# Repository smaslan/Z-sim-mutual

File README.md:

# Capacitive Reactance Simulator Based on Mutual Inductor

This project is simple simulator of capacitive rectance based on a mutual inductor.
It is just a first proof of concept prototype not inteded for direct production/replication.
See DOC for known issues and more details.

## License
The HW design is distributed under [Cern OHL license V1.2](./cern_ohl_v_1_2.pdf). 

## Acknowledgment
Presented standard design was co-developed in scope of the [EMPIR](http://msu.euramet.org/calls.html) 
project [LiBforSecUse (17IND10)](https://www.ptb.de/empir2018/libforsecuse/home/).
The project received funding from the EMPIR programme co-financed by the Participating States 
and from the European Union's Horizon 2020 research and innovation programme.

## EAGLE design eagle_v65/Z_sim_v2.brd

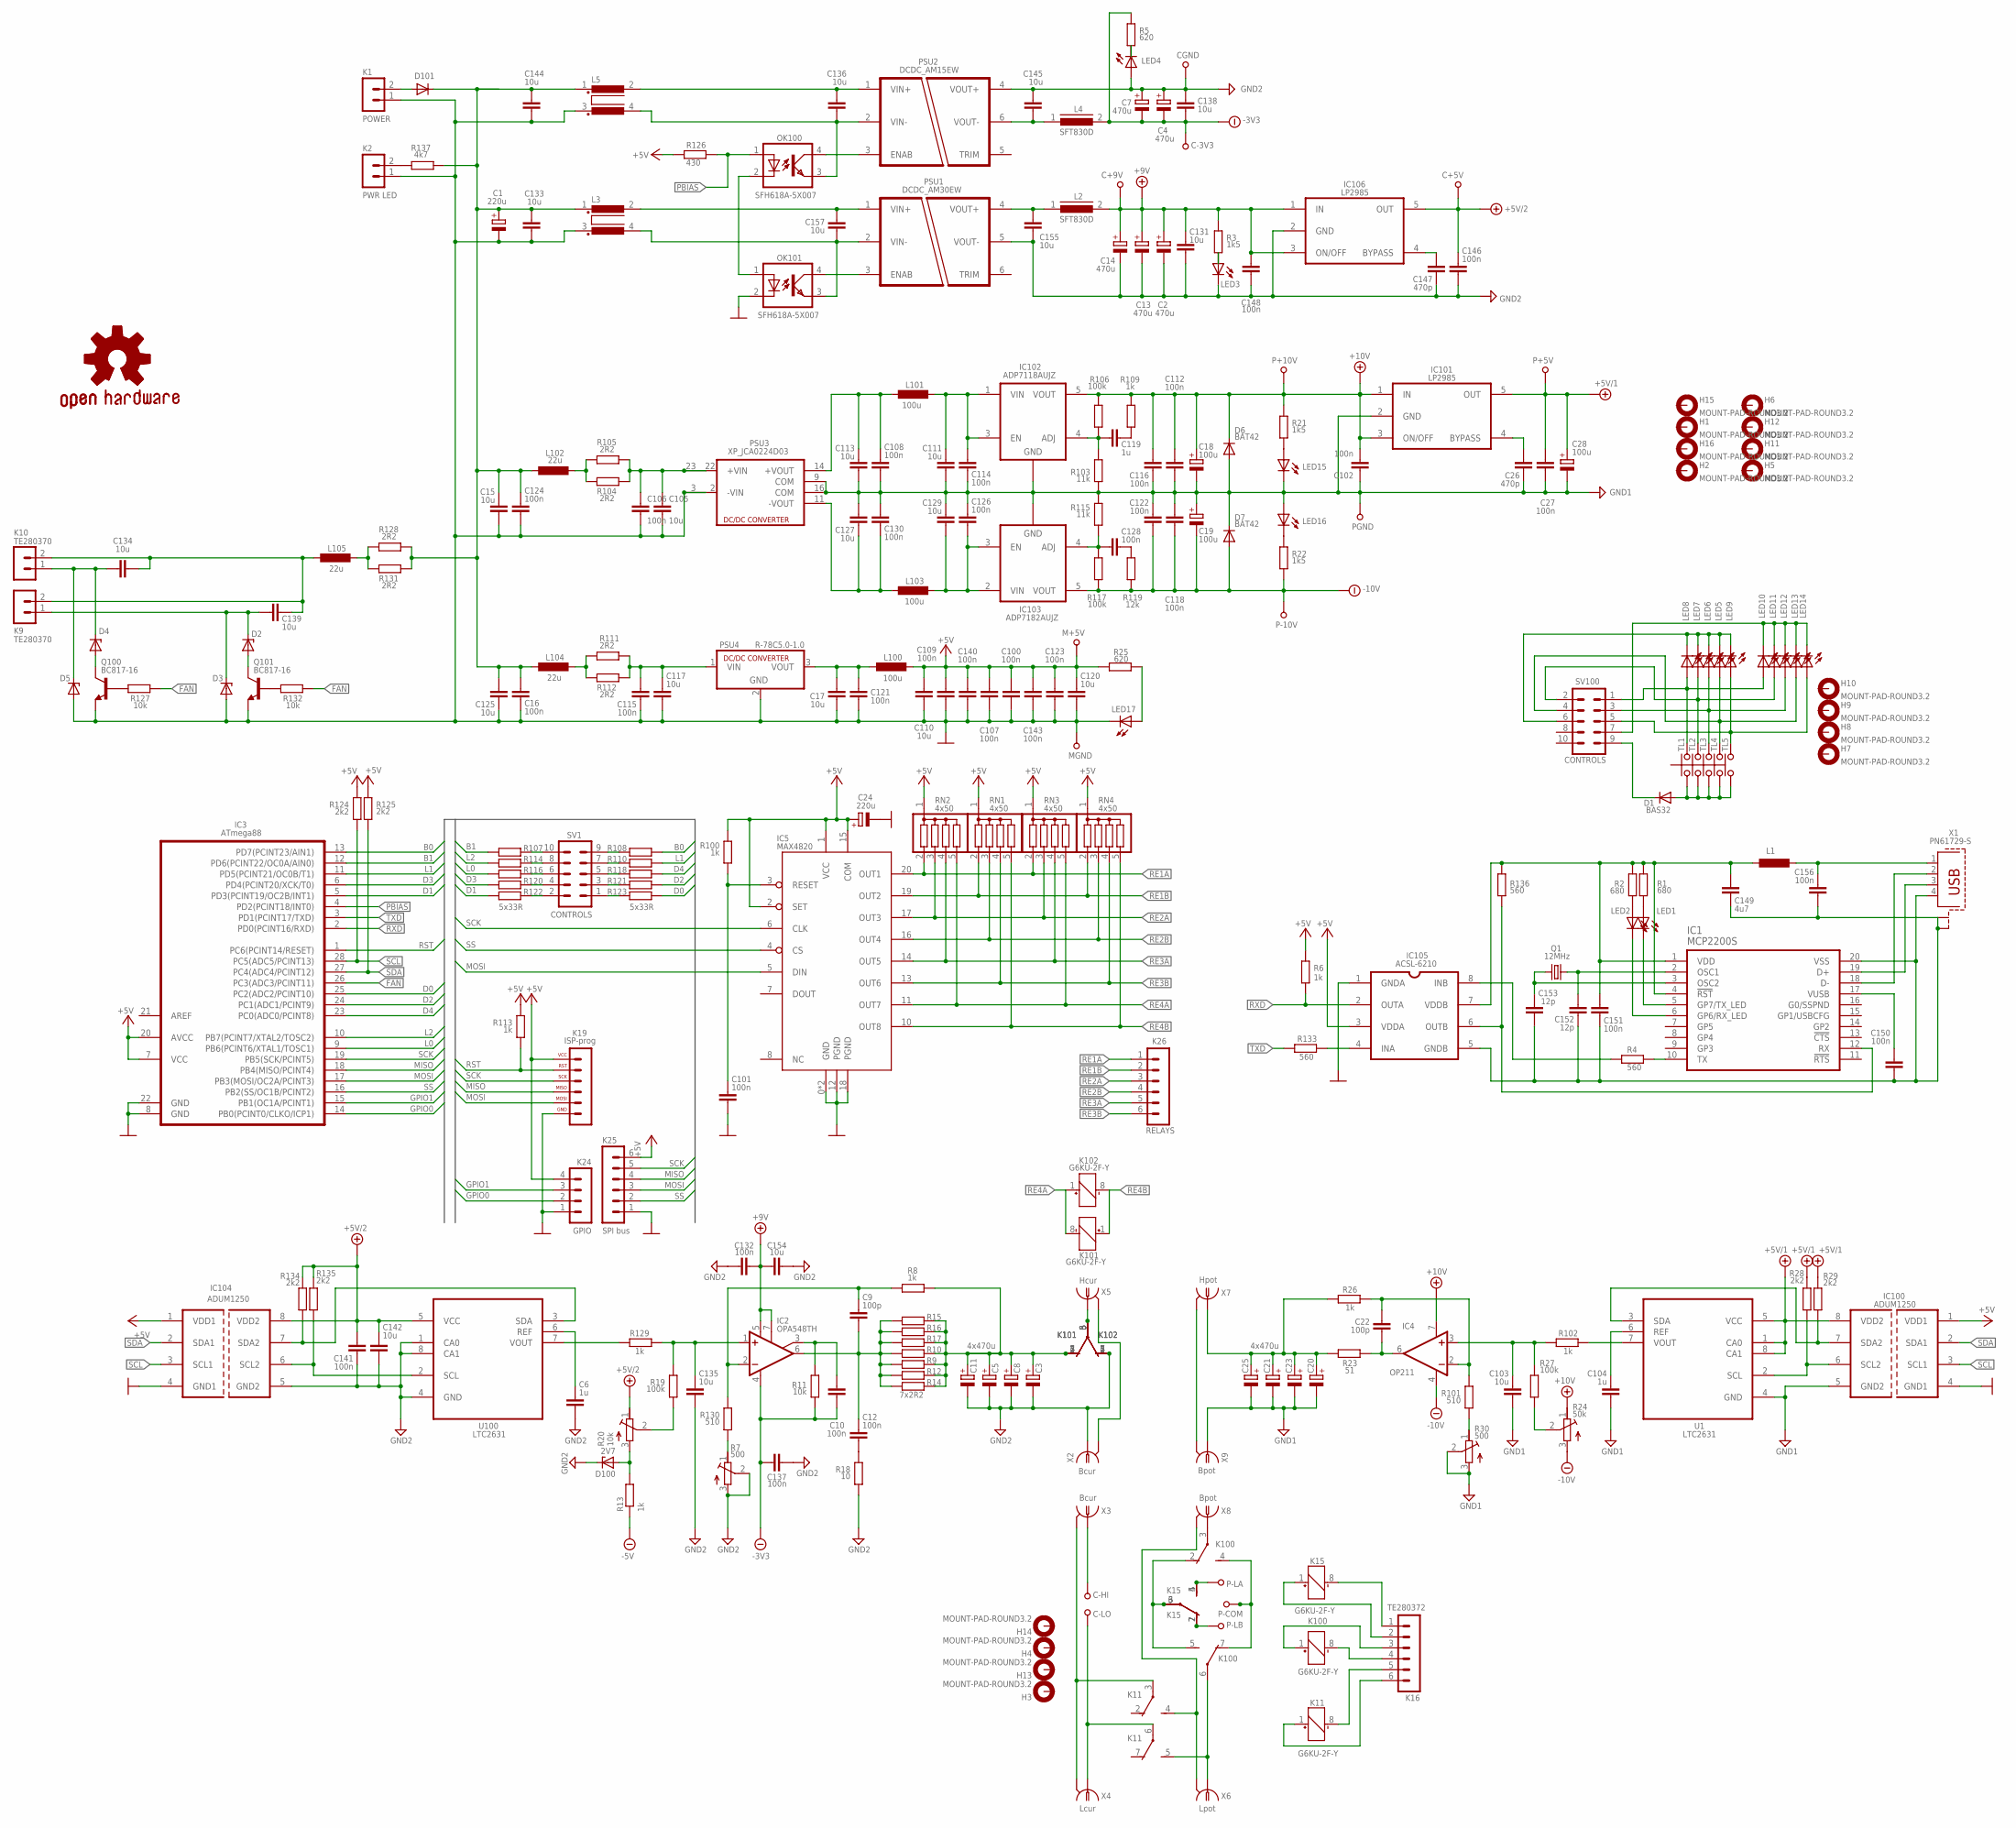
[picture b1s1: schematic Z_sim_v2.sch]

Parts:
C1, C24: 220u; E3,5-8
C2, C4, C7, C13, C14: 470u; E3,5-8
C3, C5, C8, C20, C21, C23: CPOL-EUE3.5-8; E3,5-8
C6, C104, C119: 1u; X0805
C9, C22: 100p; C025-024X044
C10, C16, C27, C100, C101, C102, C106, C107, C108, C109, C112, C114, C115, C116, C118, C121, C122, C123, C124, C126, C128, C130, C132, C137, C140, C141, C143, C146, C148, C150, C151, C156: 100n; X0805
C11, C25: 4x470u; E3,5-8
C12: 100n; C050-024X044
C15, C17, C103, C105, C110, C111, C113, C117, C120, C125, C127, C129, C131, C133, C134, C135, C136, C138, C139, C142, C144, C145, C154, C155, C157: 10u; C1210K
C18, C19, C28: 100u; E2,5-6
C26, C147: 470p; X0805
C149: 4u7; C1210K
C152, C153: 12p; X0805
C+5V, C+9V: SPL; SP
C-3V3: SPL; SP
C-HI: FAST28R; FAST28_R
C-LO: FAST28R; FAST28_R
CGND: SPL; SP
D1: BAS32; SOD80C
D2, D3, D4, D5: ZENER-DIODEZD-2.5; ZDIO-2.5
D6, D7: BAT42; SOD80C
D100: 2V7; SOD80C
D101: DIODE-MELF-MLL41; MELF-MLL41
GOLD_ORB_SM1: OSHWLOGO_GOLD_ORB_MED; OSHW1
H1, H2, H3, H4, H5, H6, H7, H8, H9, H10, H11, H12, H13, H14, H15, H16: MOUNT-PAD-ROUND3.2; 3,2-PAD
IC1: MCP2200S; SOIC20W
IC2: OPA548TH; TO220-7H
IC3: ATmega88; DIL28
IC4: OP211; DIL08
IC5: MAX4820; TSSOP20
IC100, IC104: ADUM1250; SO8
IC101, IC106: LP2985; SOT23-5
IC102: ADP7118AUJZ; SOT23-5
IC103: ADP7182AUJZ; SOT23-5
IC105: ACSL-6210; SO8
K1: POWER; TE280370
K2: PWR LED; TE280370
K9, K10: TE280370
K11, K15, K100, K101, K102: G6KU-2F-Y
K16: TE280372
K19: ISP-prog; SIL6
K24: GPIO; TE280371
K25: SPI bus; TE280372
K26: RELAYS; TE280372
L1: L-EU0204/5; 0204/5
L2, L4: SFT830D
L3, L5: R1405UB1/2; B1/2
L100, L101, L103: 100u; L1812
L102, L104, L105: 22u; L1812
LED1, LED2, LED3, LED4, LED15, LED16, LED17: LEDCHIP-LED0603; CHIP-LED0603
LED5, LED6, LED7, LED8, LED9, LED10, LED11, LED12, LED13, LED14: LED3MM
M+5V: SPL; SP
MGND: SPL; SP
OK100, OK101: SFH618A-5X007; SMD4-7
P+5V, P+10V: SPL; SP
P-10V: SPL; SP
P-COM: FAST28R; FAST28_R
P-LA: FAST28R; FAST28_R
P-LB: FAST28R; FAST28_R
PGND: SPL; SP
PSU1: DCDC_AM30EW
PSU2: DCDC_AM15EW
PSU3: XP_JCA0224D03; DCDC_XP_JCA_SYMOUT
PSU4: R-78C5.0-1.0; SIP3
Q1: 12MHz; HC49/S
Q100, Q101: BC817-16; SOT23-BEC
R1, R2: 680; X0805
R3, R21, R22: 1k5; X0805
R4, R133, R136: 560; X0805
R5, R25: 620; X0805
R6, R13, R100, R102, R109, R113, R129: 1k; X0805
R7, R30: 500; RTRIMT93YB
R8, R26: 1k; 0207/2V
R9, R10, R14, R15, R16, R17: R-EU_0207/2V; 0207/2V
R11, R127, R132: 10k; X0805
R12: 7x2R2; 0207/2V
R18: 10; 0207/2V
R19, R27: 100k; 0204V
R20: 10k; RTRIMT93YB
R23: 51; 0207/2V
R24: 50k; RTRIMT93YB
R28, R29, R124, R125, R134, R135: 2k2; X0805
R101, R130: 510; X0805
R103, R115: 11k; X0805
R104, R105, R111, R112, R128, R131: 2R2; X0805
R106, R117: 100k; X0805
R107, R123: 5x33R; X0805
R108, R110, R114, R116, R118, R120, R121, R122: R-EU_X0805; X0805
R119: 12k; X0805
R126: 430; X0805
R137: 4k7; X0805
RN1, RN2, RN3, RN4: 4x50; SIL5
SV1, SV100: CONTROLS; ML10
TL1, TL2, TL3, TL4, TL5: CUDL1_A; CUDL1
U1, U100: LTC2631; SOT65P280X100-8N
X1: PN61729-S
X2, X3: Bcur; A1944
X4: Lcur; A1944
X5: Hcur; A1944
X6: Lpot; A1944
X7: Hpot; A1944
X8, X9: Bpot; A1944

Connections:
+5V: C24.+, C100.P$1 (1), C107.P$1 (1), C109.P$1 (1), C110.1, C120.1, C123.P$1 (1), C140.P$1 (1), C143.P$1 (1), IC3.7 (VCC), IC3.20 (AVCC), IC5.1 (VCC), IC5.2 (SET), IC5.15 (COM), IC100.1 (VDD1), IC104.1 (VDD1), IC105.3 (VDDA), K19.6, K24.4, K25.6, L100.2, M+5V.1, R6.P$2 (2), R25.P$2 (2), R100.P$2 (2), R113.P$2 (2), R124.P$2 (2), R125.P$2 (2), R126.P$2 (2), RN1.1, RN2.1, RN3.1, RN4.1
+5V/1: C27.P$2 (2), C28.+, IC100.8 (VDD2), IC101.5 (OUT), P+5V.1, R28.P$2 (2), R29.P$2 (2), U1.1 (CA0), U1.5 (VCC), U1.8 (CA1)
+5V/2: C141.P$1 (1), C142.1, C146.P$2 (2), C+5V.1, IC104.8 (VDD2), IC106.5 (OUT), R20.1 (E), R134.P$2 (2), R135.P$2 (2), U100.5 (VCC)
+9V: C2.+, C13.+, C14.+, C131.1, C132.P$2 (2), C148.P$2 (2), C154.1, C+9V.1, IC2.5 (V+), IC2.7 (E/S), IC106.1 (IN), IC106.3 (ON/OFF), L2.2, R3.P$2 (2)
+10V: C18.+, C102.P$2 (2), C112.P$1 (1), C116.P$1 (1), D6.C, IC4.7 (V+), IC101.1 (IN), IC101.3 (ON/OFF), IC102.5 (VOUT), P+10V.1, R21.P$2 (2), R24.1 (E), R106.P$2 (2), R109.P$1 (1)
-5V: C4.-, C7.-, C10.P$2 (2), C137.P$1 (1), C138.2, C-3V3.1, IC2.4 (V-), L4.2, R5.P$2 (2), R11.P$2 (2), R13.P$1 (1)
-10V: C19.-, C118.P$2 (2), C122.P$2 (2), D7.A, IC4.4 (V-), IC103.5 (VOUT), P-10V.1, R22.P$2 (2), R24.3 (A), R117.P$1 (1), R119.P$2 (2)
B0: IC3.13 (PD7(PCINT23/AIN1)), R108.P$2 (2)
B1: IC3.12 (PD6(PCINT22/OC0A/AIN0)), R107.P$1 (1)
D0: IC3.25 (PC2(ADC2/PCINT10)), R123.P$2 (2)
D1: IC3.5 (PD3(PCINT19/OC2B/INT1)), R122.P$1 (1)
D2: IC3.24 (PC1(ADC1/PCINT9)), R121.P$2 (2)
D3: IC3.6 (PD4(PCINT20/XCK/T0)), R120.P$1 (1)
D4: IC3.23 (PC0(ADC0/PCINT8)), R118.P$2 (2)
FAN: IC3.26 (PC3(ADC3/PCINT11)), R127.P$1 (1), R132.P$1 (1)
GND: C1.-, C15.2, C16.P$2 (2), C17.2, C24.-, C100.P$2 (2), C101.P$2 (2), C105.2, C106.P$2 (2), C107.P$2 (2), C109.P$2 (2), C110.2, C115.P$2 (2), C117.2, C120.2, C121.P$2 (2), C123.P$2 (2), C124.P$2 (2), C125.2, C133.2, C140.P$2 (2), C143.P$2 (2), C144.2, D3.A, D5.A, IC3.8 (GND), IC3.22 (GND), IC5.0 (GND), IC5.9 (GND), IC5.12 (PGND), IC5.18 (PGND), IC100.4 (GND1), IC104.4 (GND1), IC105.1 (GNDA), K1.1, K2.1, K19.1, K24.1, K25.1, L3.3, L5.3, LED17.C, MGND.1, OK101.2 (C), PSU3.2 (-VIN), PSU3.3 (-VIN1), PSU4.2 (GND), Q100.E, Q101.E
GND1: C18.-, C19.+, C20.-, C21.-, C23.-, C25.-, C26.P$2 (2), C27.P$1 (1), C28.-, C102.P$1 (1), C103.2, C104.P$2 (2), C108.P$2 (2), C111.2, C112.P$2 (2), C113.2, C114.P$2 (2), C116.P$2 (2), C118.P$1 (1), C122.P$1 (1), C126.P$1 (1), C127.1, C129.1, C130.P$1 (1), D6.A, D7.C, IC100.5 (GND2), IC101.2 (GND), IC102.2 (GND), IC103.1 (GND), LED15.C, LED16.A, PGND.1, PSU3.9 (COM), PSU3.16 (COM), R30.2 (S), R30.3 (A), R103.P$1 (1), R115.P$2 (2), U1.4 (GND), X9.1
GND2: C2.-, C3.-, C4.+, C5.-, C6.P$2 (2), C7.+, C8.-, C11.-, C13.-, C14.-, C131.2, C132.P$1 (1), C135.2, C137.P$2 (2), C138.1, C141.P$2 (2), C142.2, C145.1, C146.P$1 (1), C147.P$2 (2), C148.P$1 (1), C154.2, C155.2, CGND.1, D100.C, IC104.5 (GND2), IC106.2 (GND), K101.4 (S), K101.5 (S), K102.2 (O), K102.7 (O), LED3.C, LED4.A, PSU1.5 (VOUT-), PSU2.4 (VOUT+), R7.2 (S), R7.3 (A), R18.1, U100.1 (CA0), U100.4 (GND), U100.8 (CA1), X2.1
GPIO0: IC3.14 (PB0(PCINT0/CLKO/ICP1)), K24.2
GPIO1: IC3.15 (PB1(OC1A/PCINT1)), K24.3
L0: IC3.9 (PB6(PCINT6/XTAL1/TOSC1)), R116.P$1 (1)
L1: IC3.11 (PD5(PCINT21/OC0B/T1)), R110.P$2 (2)
L2: IC3.10 (PB7(PCINT7/XTAL2/TOSC2)), R114.P$1 (1)
MISO: IC3.18 (PB4(MISO/PCINT4)), K19.3, K25.4
MOSI: IC3.17 (PB3(MOSI/OC2A/PCINT3)), IC5.5 (DIN), K19.2, K25.3
unnamed: C10.P$1 (1), IC2.3 (ILIM), R11.P$1 (1)
unnamed: OK100.4 (COL), PSU2.3 (ENAB)
unnamed: C135.1, IC2.1 (+IN), R19.2, R129.P$2 (2)
unnamed: C136.1, L5.2, PSU2.1 (VIN+)
unnamed: R19.1, R20.2 (S)
unnamed: C3.+, C5.+, C8.+, C11.+, K101.2 (O), K101.7 (O), K102.4 (S), K102.5 (S), R8.2, R9.2, R10.1, R12.2, R14.1, R15.2, R16.1, R17.2
unnamed: C12.2, R18.2
unnamed: C136.2, L5.4, OK100.3 (EMIT), PSU2.2 (VIN-)
unnamed: R129.P$1 (1), U100.7 (VOUT)
unnamed: C9.1, IC2.2 (-IN), R8.1, R130.P$2 (2)
unnamed: R7.1 (E), R130.P$1 (1)
unnamed: D100.A, R13.P$2 (2), R20.3 (A)
unnamed: C157.1, L3.2, PSU1.1 (VIN+)
unnamed: C157.2, L3.4, OK101.3 (EMIT), PSU1.2 (VIN-)
unnamed: K101.3, K101.6, K102.3, K102.6, X5.1
unnamed: C147.P$1 (1), IC106.4 (BYPASS)
unnamed: IC105.4 (INA), R133.P$2 (2)
unnamed: OK101.4 (COL), PSU1.3 (ENAB)
unnamed: OK100.2 (C), OK101.1 (A)
unnamed: C6.P$1 (1), U100.6 (REF)
unnamed: C139.1, D2.C, D3.C, K9.1
unnamed: C111.1, C114.P$1 (1), IC102.1 (VIN), IC102.3 (EN), L101.2
unnamed: IC104.6 (SCL2), R135.P$1 (1), U100.2 (SCL)
unnamed: IC104.7 (SDA2), R134.P$1 (1), U100.3 (SDA)
unnamed: C103.1, IC4.3 (+IN), R27.2, R102.P$2 (2)
unnamed: R24.2 (S), R27.1
unnamed: R102.P$1 (1), U1.7 (VOUT)
unnamed: C22.2, IC4.6 (OUT), R23.1
unnamed: C104.P$1 (1), U1.6 (REF)
unnamed: IC100.6 (SCL2), R28.P$1 (1), U1.2 (SCL)
unnamed: IC100.7 (SDA2), R29.P$1 (1), U1.3 (SDA)
unnamed: C126.P$2 (2), C129.2, IC103.2 (VIN), IC103.3 (EN), L103.2
unnamed: C127.2, C130.P$2 (2), L103.1, PSU3.11 (-VOUT)
unnamed: C108.P$1 (1), C113.1, L101.1, PSU3.14 (+VOUT)
unnamed: C20.+, C21.+, C23.+, C25.+, R23.2, R26.2, X7.1
unnamed: C128.P$2 (2), IC103.4 (ADJ), R115.P$1 (1), R117.P$2 (2)
unnamed: C128.P$1 (1), R119.P$1 (1)
unnamed: C119.P$2 (2), IC102.4 (ADJ), R103.P$2 (2), R106.P$1 (1)
unnamed: C119.P$1 (1), R109.P$2 (2)
unnamed: D2.A, Q101.C
unnamed: L102.2, R104.P$1 (1), R105.P$1 (1)
unnamed: C105.1, C106.P$1 (1), PSU3.22 (+VIN), PSU3.23 (+VIN1), R104.P$2 (2), R105.P$2 (2)
unnamed: C22.1, IC4.2 (-IN), R26.1, R101.P$2 (2)
unnamed: R30.1 (E), R101.P$1 (1)
unnamed: C134.1, D4.C, D5.C, K10.1
unnamed: C26.P$1 (1), IC101.4 (BYPASS)
unnamed: X7.2, X7.3 (2), X7.4 (2), X7.5 (2), X9.2, X9.3 (2), X9.4 (2), X9.5 (2)
unnamed: Q101.B, R132.P$2 (2)
unnamed: C115.P$1 (1), C117.1, PSU4.1 (VIN), R111.P$2 (2), R112.P$2 (2)
unnamed: D101.A, K1.2
unnamed: L104.2, R111.P$1 (1), R112.P$1 (1)
unnamed: C9.2, C12.1, IC2.6 (OUT), R9.1, R10.2, R12.1, R14.2, R15.1, R16.2, R17.1
unnamed: C17.1, C121.P$1 (1), L100.1, PSU4.3 (VOUT)
unnamed: X2.2, X2.3 (2), X2.4 (2), X2.5 (2), X5.2, X5.3 (2), X5.4 (2), X5.5 (2)
unnamed: C101.P$1 (1), IC5.3 (RESET), R100.P$1 (1)
unnamed: D4.A, Q100.C
unnamed: Q100.B, R127.P$2 (2)
unnamed: K2.2, R137.P$2 (2)
unnamed: R122.P$2 (2), SV1.2
unnamed: R120.P$2 (2), SV1.4
unnamed: C152.P$2 (2), IC1.2 (OSC1), Q1.2
unnamed: C153.P$2 (2), IC1.3 (OSC2), Q1.1
unnamed: C156.P$2 (2), L1.1, X1.1
unnamed: R123.P$1 (1), SV1.1
unnamed: R121.P$1 (1), SV1.3
unnamed: IC1.18 (D-), X1.2
unnamed: IC1.19 (D+), X1.3
unnamed: C150.P$2 (2), IC1.17 (VUSB)
unnamed: C149.1, C151.P$2 (2), IC1.1 (VDD), IC1.4 (!RST), IC105.7 (VDDB), L1.2, R1.P$2 (2), R2.P$2 (2), R136.P$2 (2)
unnamed: LED1.A, R1.P$1 (1)
unnamed: LED2.A, R2.P$1 (1)
unnamed: IC1.5 (GP7/TX_LED), LED1.C
unnamed: IC1.6 (GP6/RX_LED), LED2.C
unnamed: IC1.12 (RX), IC105.6 (OUTB), R136.P$1 (1)
unnamed: R118.P$1 (1), SV1.5
unnamed: IC1.10 (TX), R4.P$2 (2)
unnamed: IC105.8 (INB), R4.P$1 (1)
unnamed: C149.2, C150.P$1 (1), C151.P$1 (1), C152.P$1 (1), C153.P$1 (1), C156.P$1 (1), IC1.20 (VSS), IC105.5 (GNDB), X1.4, X1.S1, X1.S2
unnamed: R116.P$2 (2), SV1.6
unnamed: R114.P$2 (2), SV1.8
unnamed: R110.P$1 (1), SV1.7
unnamed: R107.P$2 (2), SV1.10
unnamed: R108.P$1 (1), SV1.9
unnamed: LED3.A, R3.P$1 (1)
unnamed: LED4.C, R5.P$1 (1)
unnamed: LED17.A, R25.P$1 (1)
unnamed: LED15.A, R21.P$1 (1)
unnamed: LED16.C, R22.P$1 (1)
unnamed: LED8.A, LED10.A, SV100.1, TL1.1
unnamed: LED7.A, LED11.A, SV100.2, TL2.1
unnamed: LED6.A, LED12.A, SV100.3, TL3.1
unnamed: LED5.A, LED13.A, SV100.4, TL4.1
unnamed: LED9.A, LED14.A, SV100.5, TL5.1
unnamed: K15.2 (O), K15.7 (O), P-LB.P$1
unnamed: K15.4 (S), K15.5 (S), P-LA.P$1
unnamed: D1.A, TL1.3, TL2.3, TL3.3, TL4.3, TL5.3
unnamed: D1.C, SV100.9
unnamed: LED5.K (C), LED6.K (C), LED7.K (C), LED8.K (C), LED9.K (C), SV100.6
unnamed: LED10.K (C), LED11.K (C), LED12.K (C), LED13.K (C), LED14.K (C), SV100.7
unnamed: K15.3, K15.6, K100.2 (O), K100.5 (S)
unnamed: K100.3, X8.1
unnamed: K100.4 (S), K100.7 (O), P-COM.P$1
unnamed: K16.4, K100.8 (-)
unnamed: C134.2, C139.2, K9.2, K10.2, L105.1
unnamed: K11.5 (S), K100.6, X6.1
unnamed: K11.4 (S), X6.2, X6.3 (2), X6.4 (2), X6.5 (2), X8.2, X8.3 (2), X8.4 (2), X8.5 (2)
unnamed: L105.2, R128.P$1 (1), R131.P$1 (1)
unnamed: C1.+, C15.1, C16.P$1 (1), C124.P$1 (1), C125.1, C133.1, C144.1, D101.C, L3.1, L5.1, L102.1, L104.1, R128.P$2 (2), R131.P$2 (2), R137.P$1 (1)
unnamed: C-HI.P$1, X3.1
unnamed: C-LO.P$1, K11.6, X4.1
unnamed: K11.3, X3.2, X3.3 (2), X3.4 (2), X3.5 (2), X4.2, X4.3 (2), X4.4 (2), X4.5 (2)
unnamed: K15.1 (+), K16.2
unnamed: K15.8 (-), K16.1
unnamed: K16.3, K100.1 (+)
unnamed: K11.1 (+), K16.6
unnamed: K11.8 (-), K16.5
PBIAS: IC3.4 (PD2(PCINT18/INT0)), OK100.1 (A), R126.P$1 (1)
RE1A: IC5.20 (OUT1), K26.1, RN2.2, RN3.2
RE1B: IC5.19 (OUT2), K26.2, RN1.2, RN4.2
RE2A: IC5.17 (OUT3), K26.3, RN2.3, RN3.3
RE2B: IC5.16 (OUT4), K26.4, RN1.3, RN4.3
RE3A: IC5.14 (OUT5), K26.5, RN2.4, RN3.4
RE3B: IC5.13 (OUT6), K26.6, RN1.4, RN4.4
RE4A: IC5.11 (OUT7), K101.8 (-), K102.1 (+), RN2.5, RN3.5
RE4B: IC5.10 (OUT8), K101.1 (+), K102.8 (-), RN1.5, RN4.5
RST: IC3.1 (PC6(PCINT14/RESET)), K19.5, R113.P$1 (1)
RXD: IC3.2 (PD0(PCINT16/RXD)), IC105.2 (OUTA), R6.P$1 (1)
SCK: IC3.19 (PB5(SCK/PCINT5)), IC5.6 (CLK), K19.4, K25.5
SCL: IC3.28 (PC5(ADC5/PCINT13)), IC100.3 (SCL1), IC104.3 (SCL1), R124.P$1 (1)
SDA: IC3.27 (PC4(ADC4/PCINT12)), IC100.2 (SDA1), IC104.2 (SDA1), R125.P$1 (1)
SS: IC3.16 (PB2(SS/OC1B/PCINT2)), IC5.4 (CS), K25.2
TXD: IC3.3 (PD1(PCINT17/TXD)), R133.P$1 (1)
VOUT+: C155.1, L2.1, PSU1.4 (VOUT+)
VOUT-: C145.2, L4.1, PSU2.6 (VOUT-)

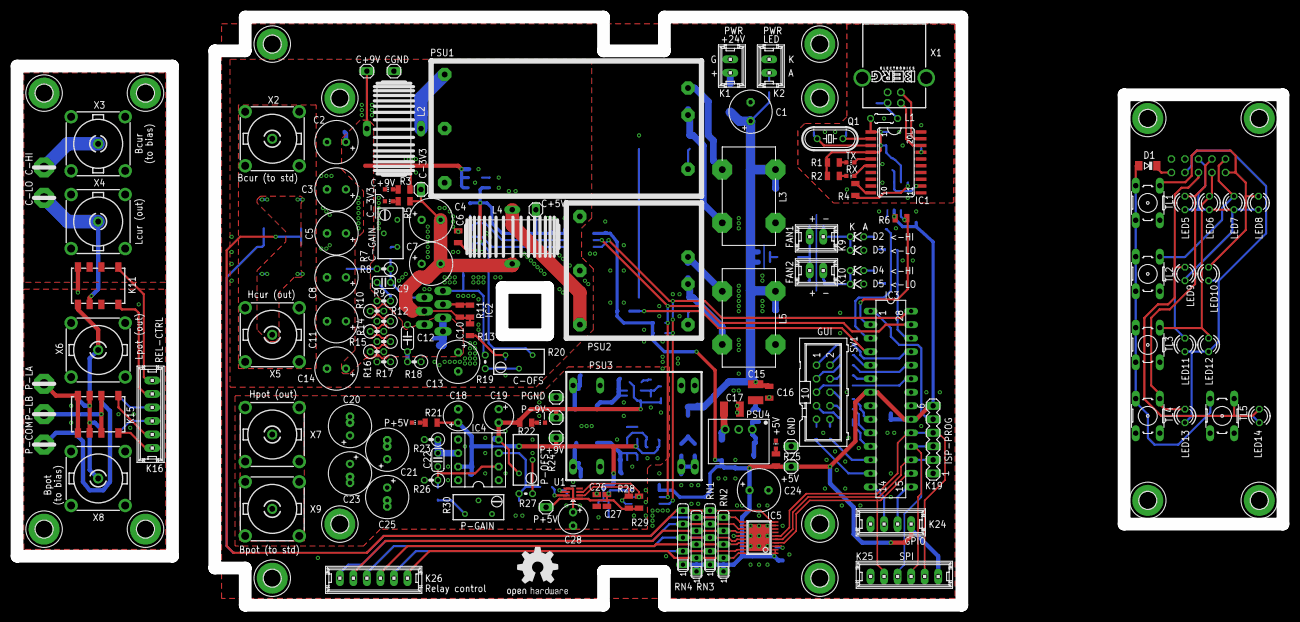
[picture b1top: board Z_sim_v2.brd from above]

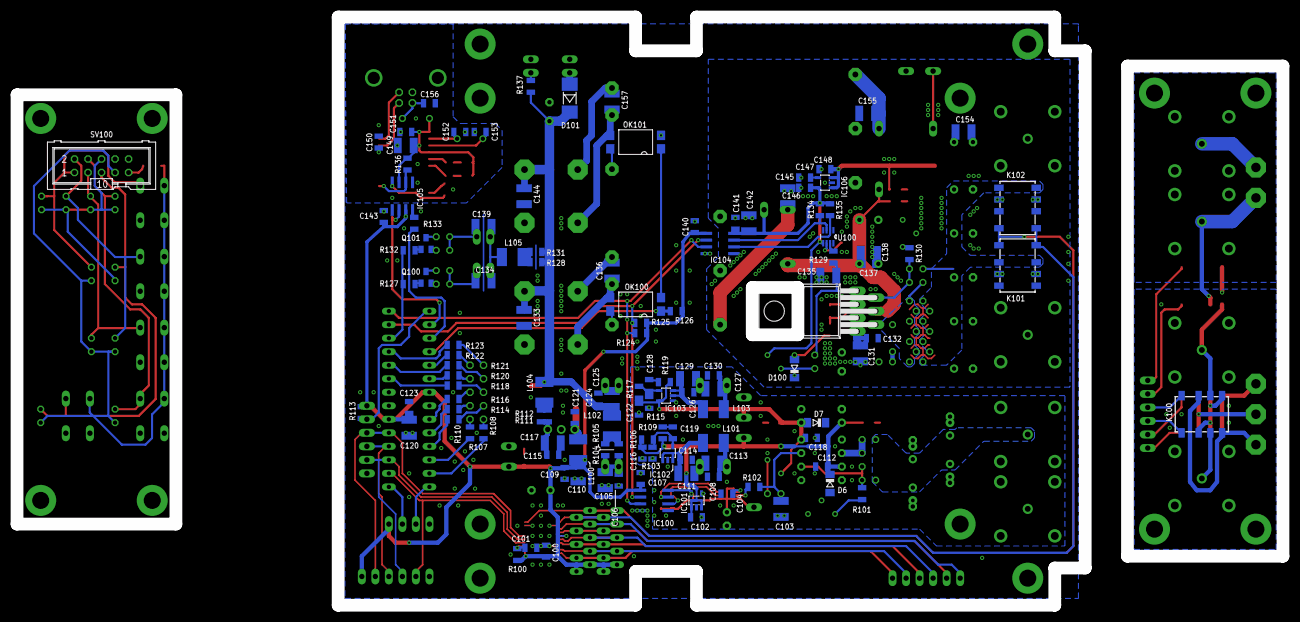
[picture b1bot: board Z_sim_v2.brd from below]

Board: 2 copper layers, 140.3 x 110.5 mm, 280 parts (122 on the bottom side), 159 nets.

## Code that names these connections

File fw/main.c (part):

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// power bias control (active low)
#define PBIASp PORTD
#define PBIASd DDRD
#define PBIAS PD2

// FAN control
#define PFANp PORTC
#define PFANd DDRC
#define PFAN PC3

// main timer tick [s]
#define MTICK 500e-6
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// SPI bus states
#define SPID DDRB
#define SPIP PORTB
#define SS PB2
#define SCK PB5
#define MOSI PB3

// send special relays MAX4820 controler command via SPI
void spec_relay_set(uint8_t data)
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// button commons
#define MB0p PORTD
#define MB0d DDRD
#define MB0  PD7
#define MB1p PORTD
#define MB1d DDRD
#define MB1  PD6
// LED cathodes
#define ML0p PORTB
#define ML0d DDRB
#define ML0  PB6
#define ML1p PORTD
#define ML1d DDRD
#define ML1  PD5
#define ML2p PORTB
#define ML2d DDRB
#define ML2  PB7
// LED anodes/buttons
#define MD0p PORTC
#define MD0i PINC
#define MD0d DDRC
#define MD0  PC2
#define MD1p PORTD
#define MD1i PIND
#define MD1d DDRD
#define MD1  PD3
#define MD2p PORTC
#define MD2i PINC
#define MD2d DDRC
#define MD2  PC1
#define MD3p PORTD
#define MD3i PIND
#define MD3d DDRD
#define MD3  PD4
#define MD4p PORTC
#define MD4i PINC
#define MD4d DDRC
#define MD4  PC0

#define LED_CYCLES 1
#define LED_DEADTIME 5
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	TWCR = (1<<TWEN)|(1<<TWEA);
	TWBR = (uint8_t)((F_CPU - 16.0*I2C_FREQ)/(2.0*I2C_FREQ));
	TWSR = (0<<TWPS0);
	PORTC |= (1<<PC4) | (1<<PC5);

	// clear states
	ctrl.bias = 0;
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
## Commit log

2020-01-26 add: basic info
2020-02-03 add: EAGLE data and DOC
    - possibly not final version!
2020-02-14 add: fw, more doc
2020-02-14 fix: doc: SCPI commands termination CR changed to LF
2020-02-17 add: bootloader, updated doc
2021-03-22 fix: updated doc

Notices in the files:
fw/main.c:
(c) 2020, Stanislav Maslan, CMI, smaslan@cmi.cz, s.maslan@seznam.cz
The code is distributed under MIT license, https://opensource.org/licenses/MIT.
